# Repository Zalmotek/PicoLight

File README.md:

# PicoLight 🌈

✨ PicoLight is a minimalist adjustable light for low-light photography, based on the Raspberry Pi Pico.

✨ For more details check out the project documentation on [Hackaday](https://hackaday.io/project/182069-picolight-minimalist-light-for-product-shots).

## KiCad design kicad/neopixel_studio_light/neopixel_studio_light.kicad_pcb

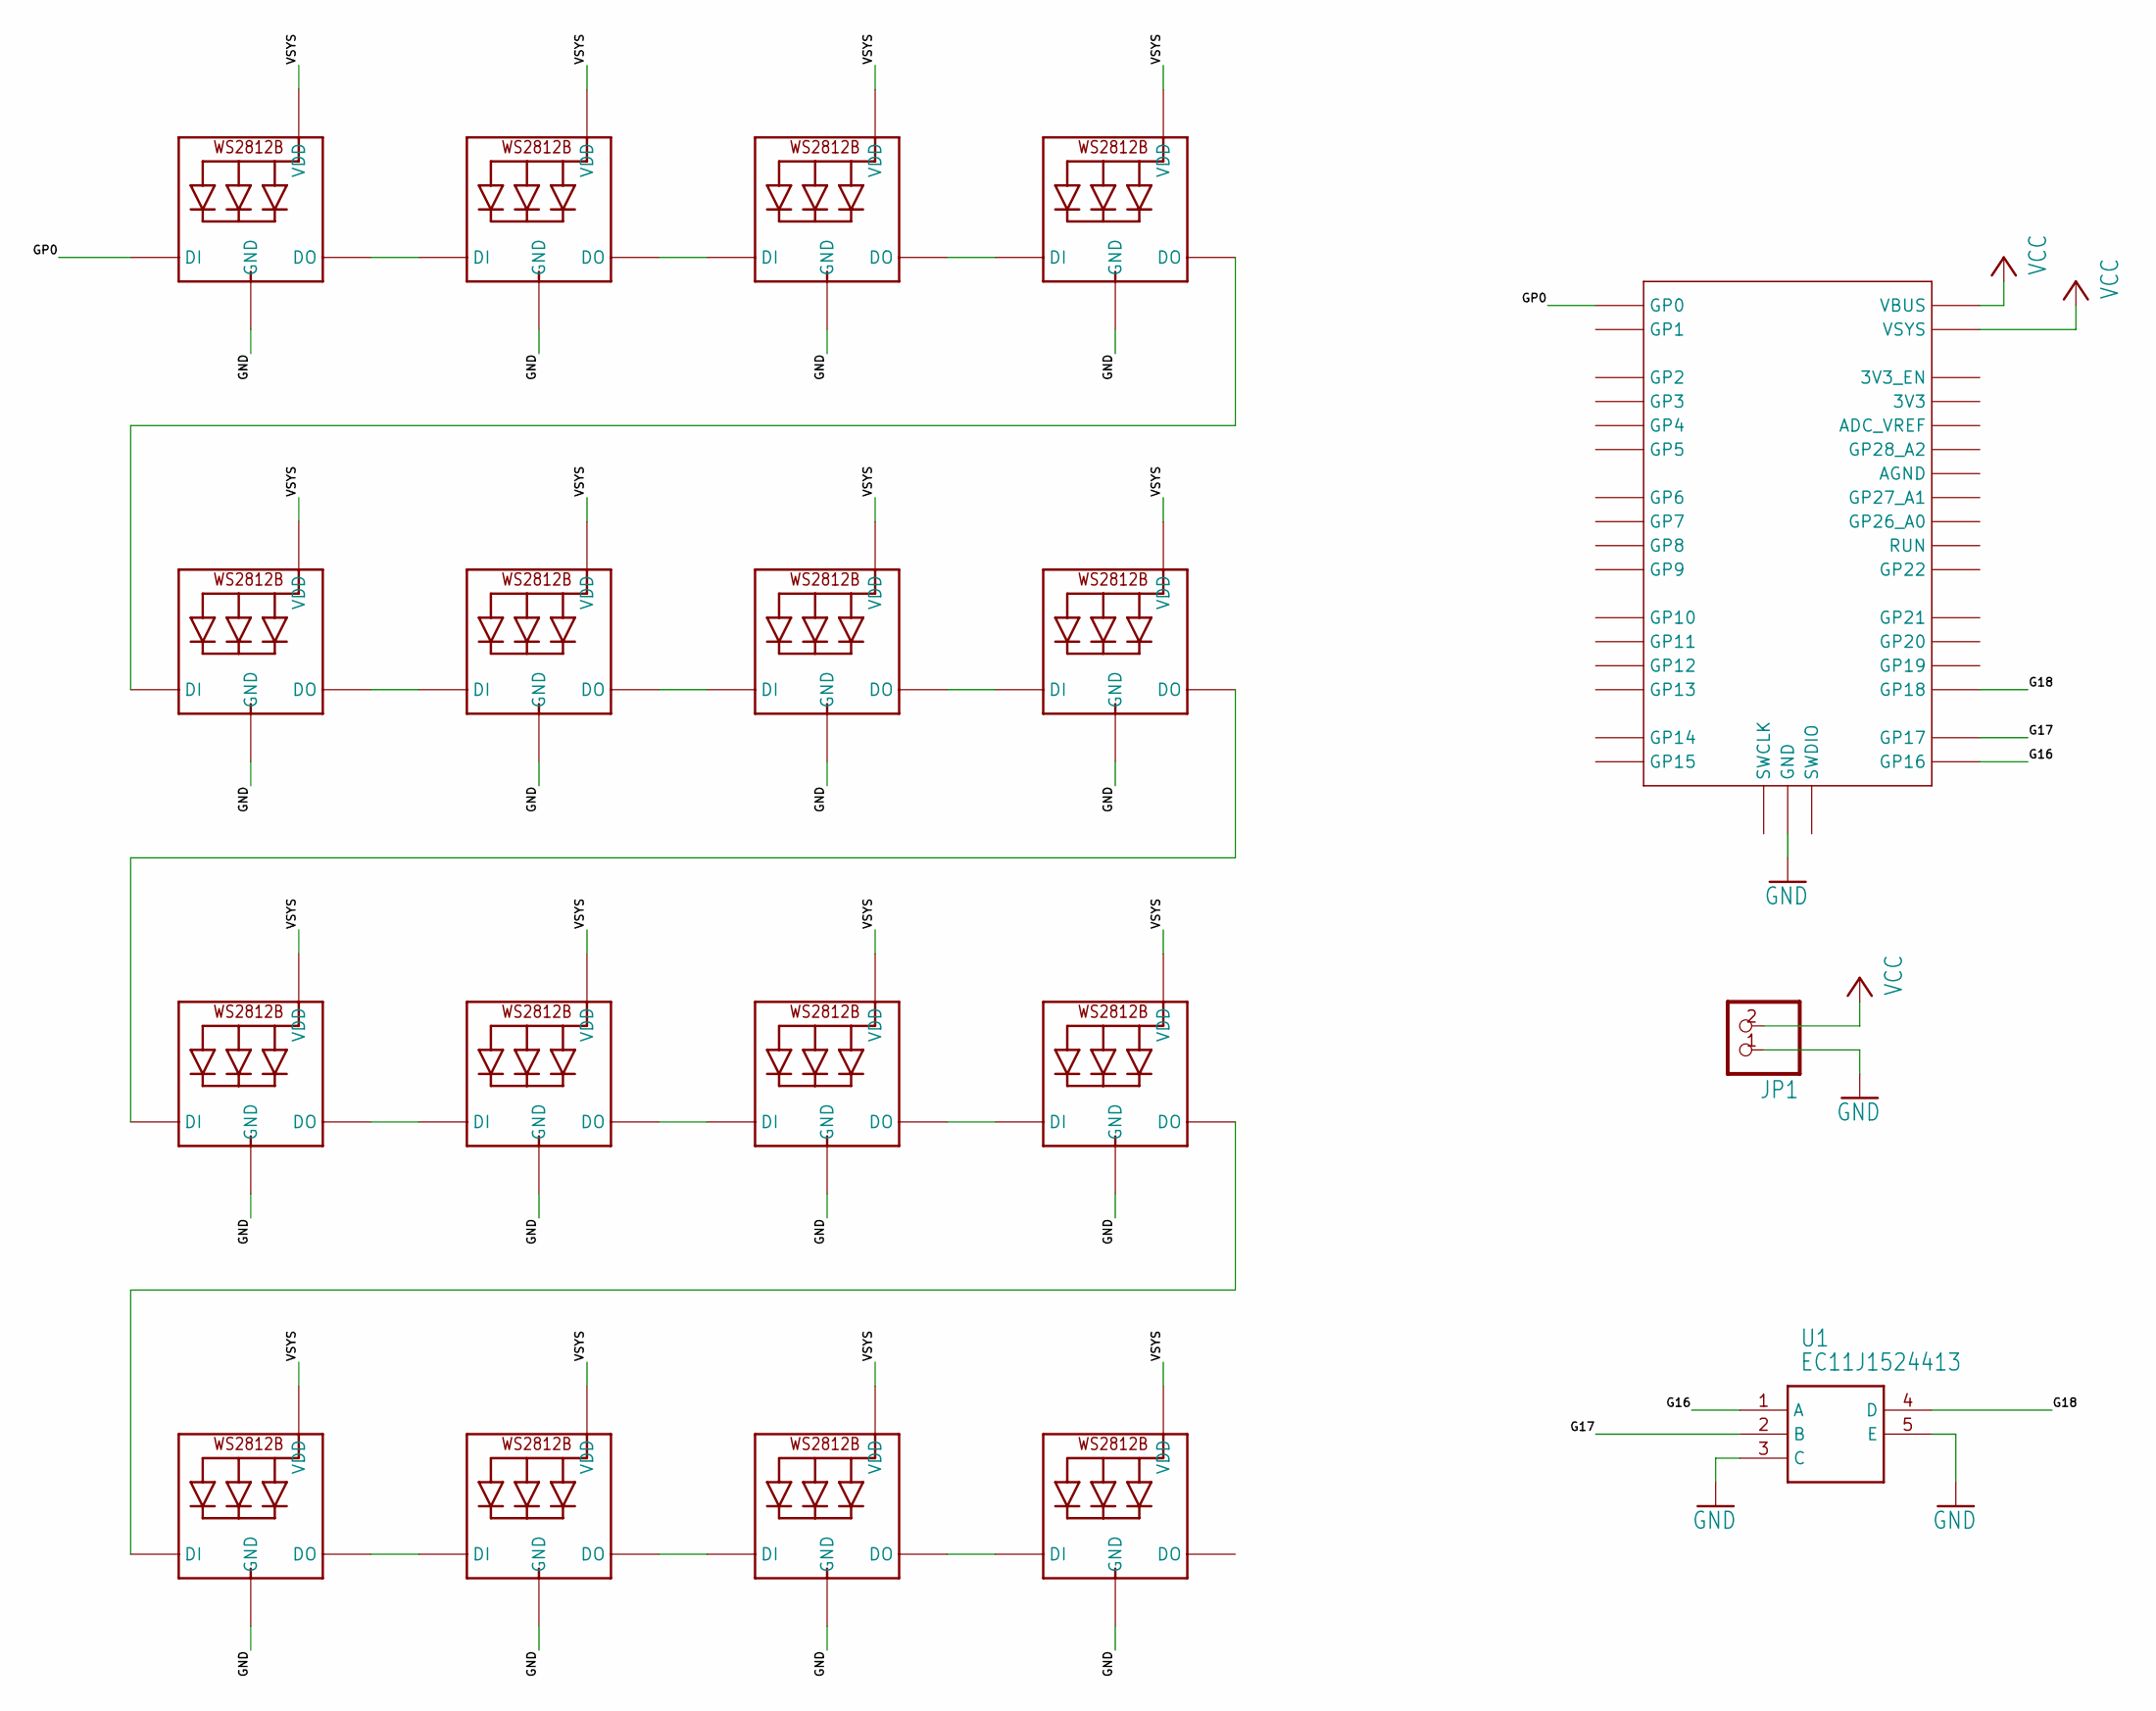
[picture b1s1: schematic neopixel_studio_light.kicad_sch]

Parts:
JP1: PINHD-1X2; 1X02
LED1, LED2, LED3, LED4, LED5, LED6, LED7, LED8, LED9, LED10, LED11, LED12, LED13, LED14, LED15, LED16: WS2812B5050; WS2812B
U1: EC11J1524413
U$1: RPI_PICO-SMD; RPI_PICO

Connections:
/G16: U1.1 (A), U$1.GP16
/G17: U1.2 (B), U$1.GP17
/G18: U1.4 (D), U$1.GP18
/GP0: LED1.4-DIN (DI), U$1.GP0
/VSYS: LED1.1-VDD (VDD), LED2.1-VDD (VDD), LED3.1-VDD (VDD), LED4.1-VDD (VDD), LED5.1-VDD (VDD), LED6.1-VDD (VDD), LED7.1-VDD (VDD), LED8.1-VDD (VDD), LED9.1-VDD (VDD), LED10.1-VDD (VDD), LED11.1-VDD (VDD), LED12.1-VDD (VDD), LED13.1-VDD (VDD), LED14.1-VDD (VDD), LED15.1-VDD (VDD), LED16.1-VDD (VDD)
GND: JP1.1, LED1.3-GND (GND), LED2.3-GND (GND), LED3.3-GND (GND), LED4.3-GND (GND), LED5.3-GND (GND), LED6.3-GND (GND), LED7.3-GND (GND), LED8.3-GND (GND), LED9.3-GND (GND), LED10.3-GND (GND), LED11.3-GND (GND), LED12.3-GND (GND), LED13.3-GND (GND), LED14.3-GND (GND), LED15.3-GND (GND), LED16.3-GND (GND), U1.3 (C), U1.5 (E), U$1.GND@1 (GND), U$1.GND@2 (GND), U$1.GND@3 (GND), U$1.GND@4 (GND), U$1.GND@5 (GND), U$1.GND@6 (GND), U$1.GND@7 (GND), U$1.GND@8 (GND)
unnamed: LED1.2-DOUT (DO), LED2.4-DIN (DI)
unnamed: LED2.2-DOUT (DO), LED3.4-DIN (DI)
unnamed: LED3.2-DOUT (DO), LED4.4-DIN (DI)
unnamed: LED4.2-DOUT (DO), LED5.4-DIN (DI)
unnamed: LED5.2-DOUT (DO), LED6.4-DIN (DI)
unnamed: LED6.2-DOUT (DO), LED7.4-DIN (DI)
unnamed: LED7.2-DOUT (DO), LED8.4-DIN (DI)
unnamed: LED8.2-DOUT (DO), LED9.4-DIN (DI)
unnamed: LED9.2-DOUT (DO), LED10.4-DIN (DI)
unnamed: LED10.2-DOUT (DO), LED11.4-DIN (DI)
unnamed: LED11.2-DOUT (DO), LED12.4-DIN (DI)
unnamed: LED12.2-DOUT (DO), LED13.4-DIN (DI)
unnamed: LED13.2-DOUT (DO), LED14.4-DIN (DI)
unnamed: LED14.2-DOUT (DO), LED15.4-DIN (DI)
unnamed: LED15.2-DOUT (DO), LED16.4-DIN (DI)
VCC: JP1.2, U$1.VBUS, U$1.VSYS

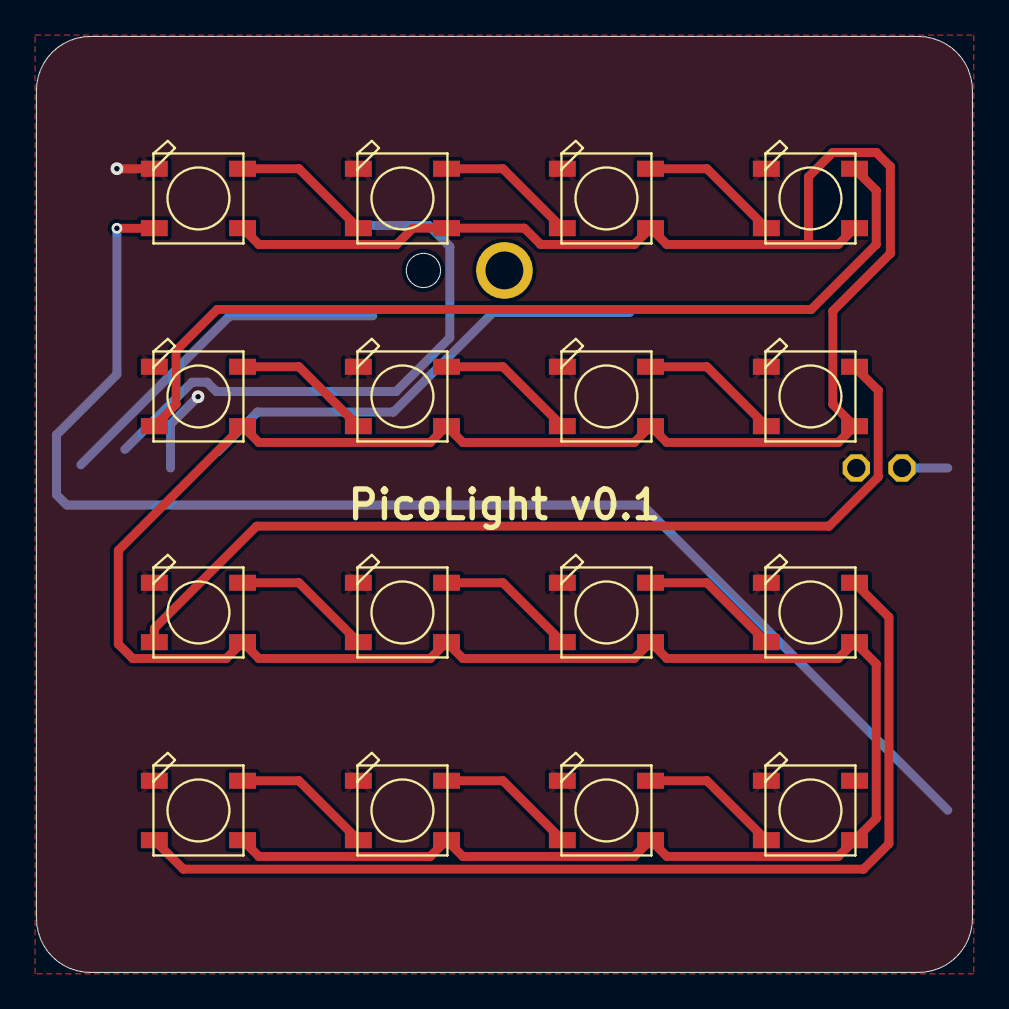
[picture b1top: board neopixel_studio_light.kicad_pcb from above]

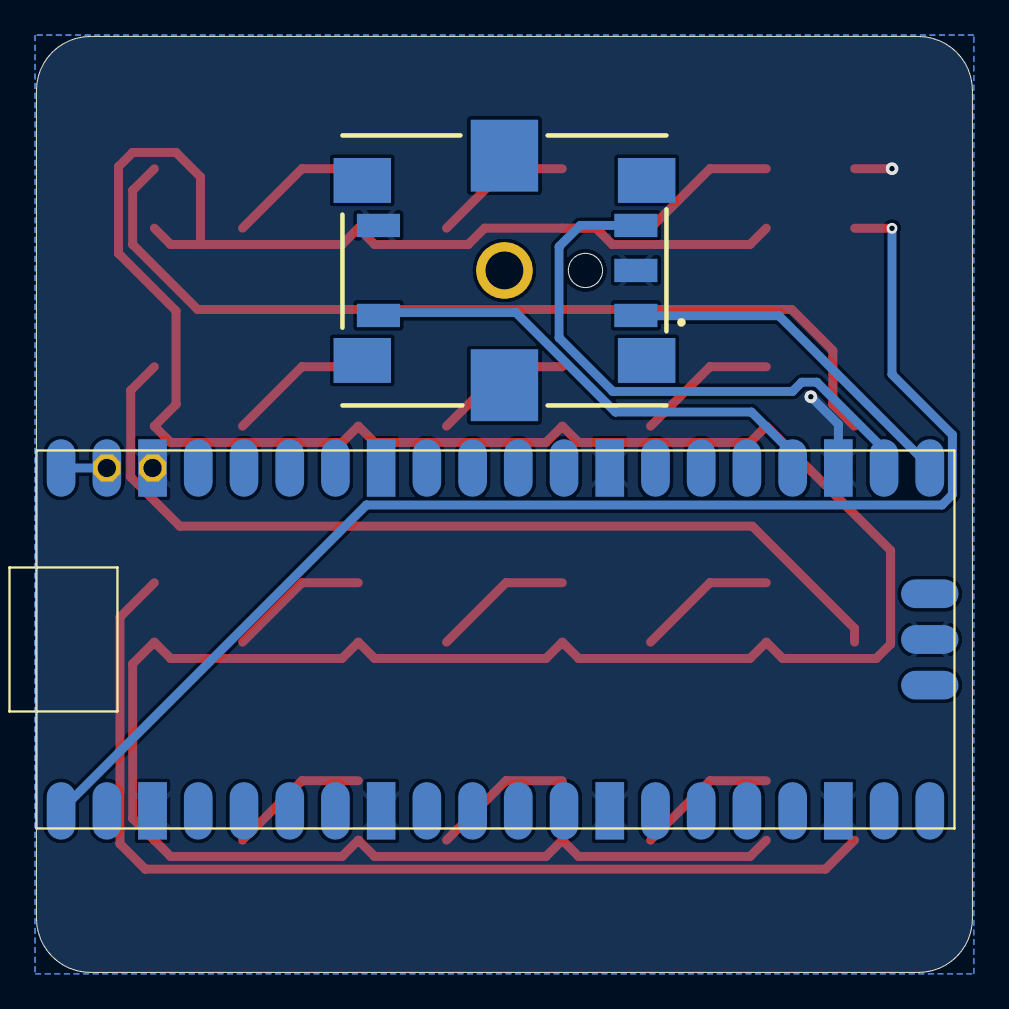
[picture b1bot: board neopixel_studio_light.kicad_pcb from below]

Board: 2 copper layers, 52.0 x 52.0 mm, 19 parts (2 on the bottom side), 22 nets.

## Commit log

2021-10-04 resized image
2021-10-05 Create LICENSE
2021-10-27 added circuit python libraries + gerber files
2021-11-05 added cover laser cut file
2023-08-21 kicad files, needs mounting holes
